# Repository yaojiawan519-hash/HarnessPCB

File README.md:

# HarnessPCB

**在自己的 Claude Code 里设计 PCB**：喂三段意图报告（原理图设计表 / 放置意图 /
布线意图），LLM 决策层调度执行器完成全链，产出可送厂的 Gerber。

> 状态：🟢 P0–P5 已完成（执行器抽取 + 双仓字节级复现 + 8 Skills + plugin 骨架
> + MCP server 随包 + 数据剥离审计 + MIT 许可；**P5 = 退役 RL 放置线、换规则摆件、
> 108 块人画电路块随包**），当前 **v0.2**。

## 快速开始（一屏）

前置：KiCad 10、Java 25+、FreeRouting v2.3.0（jar 从
[GitHub Releases](https://github.com/freerouting/freerouting/releases) 下，
放大磁盘任意位置）、Node 18+、[uv](https://docs.astral.sh/uv/)。

```bash
git clone <本仓库> && cd HarnessPCB

# 1. 装依赖（生成 executors/Placement/.venv；v0.2 起不再需要 torch——放置是纯规则）
cd executors/Placement && uv sync && cd ../..

# 2. 写本机工具路径（通常只需改 java / jar 两键；MCP server 已随包）
cat > ~/.harnesspcb.json <<'EOF'
{
  "HWS_KICAD_CLI": "/Applications/KiCad/KiCad.app/Contents/MacOS/kicad-cli",
  "HWS_KICAD_PY":  "/Applications/KiCad/KiCad.app/Contents/Frameworks/Python.framework/Versions/3.9/bin/python3.9",
  "HWS_KICAD_EXT": "/Applications/KiCad/KiCad.app/Contents",
  "HWS_JAVA": "/opt/homebrew/opt/openjdk@26/bin/java",
  "HWS_FREEROUTING_JAR": "/path/to/freerouting.jar",
  "D2S_MCP": "<克隆目录>/mcp/server/index.mjs",
  "D2S_NODE": "/opt/homebrew/bin/node"
}
EOF

# 3. 体检（全绿才继续；三级解析：环境变量 > 此文件 > 标准探测）
executors/Placement/.venv/bin/kca doctor

# 4. 跑包内 demo 全链（设计表 → 原理图 → 放置 → 布线 → 铺铜 → DRC）
python3 executors/SchematicDesign/design2schematic/d2s.py chain \
  -d demo/demo_blinker.design.json -o demo/out \
  --clearances 205,215,225,235,245 --mp 60
```

demo 是什么、期望产物链，见 `demo/README.md`。全绿后按
`skills/pcb-fab-export` 出 Gerber。设计表写法看 `docs/输入格式说明.md`。

## 装成 Claude Code 插件

上面是裸 CLI 形态。装成插件后，Skills 与斜杠命令自动可用：

```bash
# 方式 A：本地路径（开发/试用）
claude plugin marketplace add /path/to/HarnessPCB
claude plugin install harnesspcb@harnesspcb

# 方式 B：git URL（仓库推上远端后）
claude plugin marketplace add <git-url>
claude plugin install harnesspcb@harnesspcb
```

装好后在本项目里：

| 命令 | 干什么 |
|---|---|
| `/harnesspcb:pcb-demo` | 跑包内 demo 全链，验证环境 |
| `/harnesspcb:pcb-run <design.json>` | 跑一块用户板全链（可带 `--intent`） |
| `/harnesspcb:pcb-new [需求]` | 从需求访谈 → 设计表 → 意图 → 全链出板 |

8 个 Skills（`pcb-chain` / `pcb-place` / `pcb-route` / `pcb-route-session` /
`pcb-intent-spec` / `pcb-drc-read` / `pcb-silk-tidy` / `pcb-fab-export`）
随插件自动装配；裸 CLI 形态则把 `skills/` 拷（或 symlink）进项目
`.claude/skills/`。各 skill 何时用见下表。

## Skills 一览（8 个）

| Skill | 何时用 |
|---|---|
| `pcb-chain` | 一条命令全链（sch→board→place→route→pour→DRC），默认入口 |
| `pcb-place` / `pcb-route` | 单独重跑放置（规则摆件，调 `--face`/`--gap`/`--ports`）/ 布线（调阶梯、看真数） |
| `pcb-route-session` | 剩余死网手术：candidates/blockers/单网重布/快照回滚 |
| `pcb-intent-spec` | 放置的写前清单 + 交付审查对照（原「意图 spec」，spec 本身已停用） |
| `pcb-drc-read` | DRC 报告口径（铜级 9 类 / 容忍项 / fail-closed） |
| `pcb-silk-tidy` | 丝印清理五条方法学（美观项，不挡验收） |
| `pcb-fab-export` | Gerber + 钻孔 + 贴片坐标导出打包 |

## 块库（108 块）

`blocks/` 里是从真实开源板**一件一件、一截铜一截铜扣下来**的电路：原理图、封装、
人手画的走线原封不动。设计新板时当**菜单**用——能整块复用的别重画。

```bash
ls blocks/                      # 每块一个目录
cat blocks/INDEX.md             # 人看：块名 / 类别 / 件数 / 铜量 / 来源板 / 许可
python3 -c "import json;[print(b['name'],b['category']) for b in json.load(open('blocks/index.json'))['blocks']]"
```

每块带块卡（端口 / 轨 / 内部网 / 出处与许可）与实测几何。**口岸按焊盘记**：
拼板时从焊盘重新拉线，不指望块里切剩的出口铜对接上。GND 与电源轨在块里是裂开的
（块不带铺铜），拼板必须整板重铺。规矩与坑详见 `docs/块库说明.md`。

只收可公开发行的块（MIT/Apache 等）；用户自己的板与许可未核定的块**不在本仓库**。

## 仓库结构

| 目录 | 内容 |
|---|---|
| `skills/` | 8 个操作 Skills（上表） |
| `commands/` | 插件斜杠命令（pcb-demo / pcb-run / pcb-new） |
| `.claude-plugin/` + `.mcp.json` | Claude Code plugin 清单与 MCP 声明 |
| `mcp/` | 随包 KiCad MCP server（单文件 bundle + python 接口层，源自 KiCAD-MCP-Server v2.7.0，MIT，见 `mcp/LICENSE-KiCAD-MCP-Server`） |
| `executors/` | 白名单抽取的执行器（d2s / 规则摆件 place_rules / route 冻结梯子 / actions / 块工具链 sdi + IL 解析层），`MANIFEST.json` 逐文件 sha256 |
| `blocks/` | **108 块人画电路块**（原理图 + 板 + 块卡 + 实测几何），可整块复用；见 `docs/块库说明.md` |
| `docs/` | 输入格式说明、块库说明、参数快照 FLAG_FREEZE |
| `demo/` | 合成 demo 板（设计表 + 期望产物说明） |
| `tools/` | 抽取脚本（`pack_from_studio.py` + allowlist、`pack_blocks.py`） |

## 同步机制（贡献者向）

```bash
python3 tools/pack_from_studio.py --check   # 看差异（缺/多/变动）
python3 tools/pack_from_studio.py --sync    # 重生成 executors/ + MANIFEST.json

python3 tools/pack_blocks.py --list         # 谁进包、谁被许可证挡下
python3 tools/pack_blocks.py --check        # 块库差异
python3 tools/pack_blocks.py --sync         # 重生成 blocks/ + 索引 + MANIFEST-blocks.json
```

块库**按许可证筛**而不是按路径：只收 `license_tier: permissive`，`internal`
（用户自己的板 / 许可未核定）与无块卡的老块整批拒绝——公开仓放不起这个错。

`executors/` 由抽取脚本从开发工作台（母舰）生成，**禁止手改**（下次同步会被
覆盖）；`skills/`、`docs/`、`demo/`、`commands/`、`.claude-plugin/` 的权威源
在本仓库，直接在此编写。一切代码与测试在母舰工作台进行，单向同步进本仓库，
绝不反向修改。allowlist 从 Skills 调用面自下而上反推（`tools/allowlist.txt`
是唯一清单源），评估产物 / 用户板 / RL 权重 / 研究脚本结构上就进不来。

## 外部依赖与版本口径

| 依赖 | 版本口径 | 用途 |
|---|---|---|
| KiCad | 10（macOS Apple Silicon 实测；他平台未验） | pcbnew Python API、kicad-cli |
| FreeRouting | **v2.3.0 钉死**（需 Java 25+，调用内部钉单线程） | 布线 |
| KiCAD-MCP-Server | v2.7.0（已随包 bundle，MIT） | 原理图步的 KiCad 桥 |
| Node | 18+（实测 25） | 起 MCP server |
| uv | 任意近期版 | 建 Python 环境 |

## 许可

- 本仓库代码与文档：**MIT**（见根目录 `LICENSE`）。
- 随包 `mcp/`：源自 KiCAD-MCP-Server（MIT），原许可文件保留于
  `mcp/LICENSE-KiCAD-MCP-Server`。
- **FreeRouting 不随包分发**：它是 GPL-3.0，与本包 MIT 不兼容，故 jar
  由使用者自行从官方 [GitHub Releases](https://github.com/freerouting/freerouting/releases)
  下载，包内只含调用接口（`HWS_FREEROUTING_JAR` 指向你自己的 jar）。

所有工具路径**三级解析**：环境变量（`HWS_*` / `D2S_*`）> 机器配置文件
`~/.harnesspcb.json`（`HWS_CONFIG` 可改指）> 标准探测（PATH / 常见安装位）。
`kca doctor` 一条命令体检全链缺项。推荐档参数以
`docs/参数快照_FLAG_FREEZE.md` 为唯一权威源。

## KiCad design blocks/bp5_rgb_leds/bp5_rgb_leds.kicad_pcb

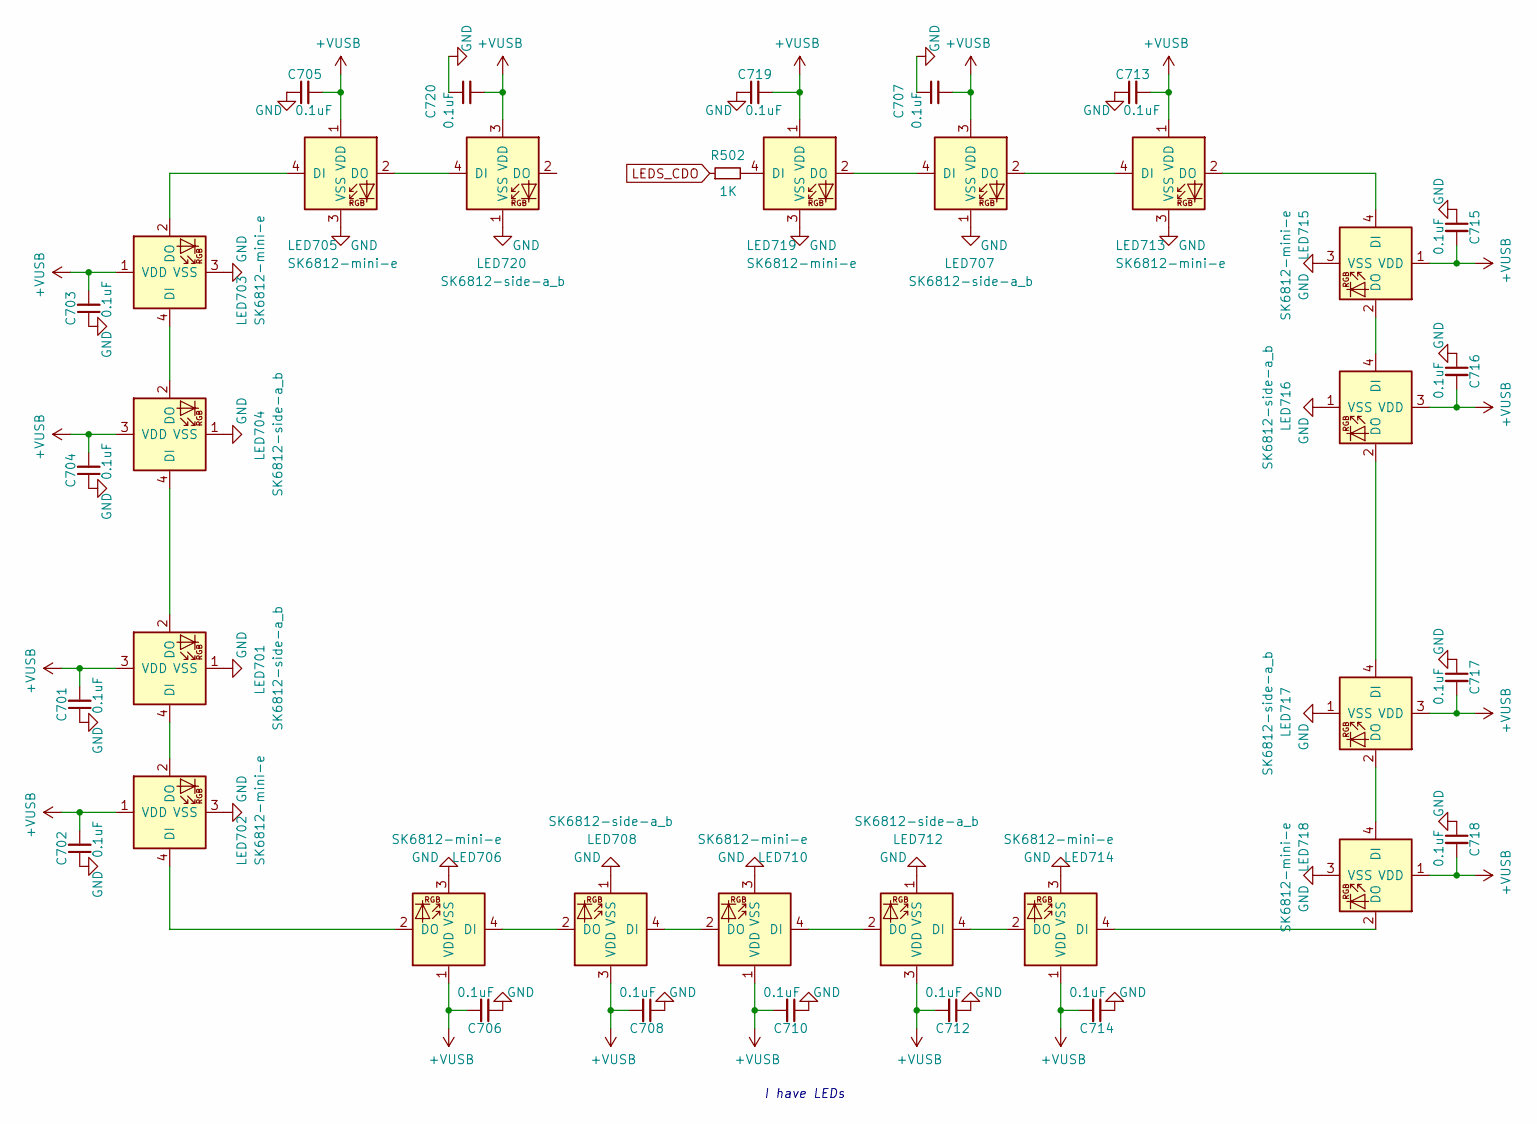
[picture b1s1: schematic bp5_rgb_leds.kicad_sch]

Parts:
C701, C702, C703, C704, C705, C706, C707, C708, C710, C712, C713, C714, C715, C716, C717, C718, C719, C720: 0.1uF; C_0402_1005Metric
LED701, LED704, LED707, LED708, LED712, LED716, LED717, LED720: SK6812-side-a_b
LED702, LED703, LED705, LED706, LED710, LED713, LED714, LED715, LED718, LED719: SK6812-mini-e
R502: 1K; R_0402_1005Metric

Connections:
+VUSB: C701.2, C702.2, C703.2, C704.2, C705.2, C706.2, C707.2, C708.2, C710.2, C712.2, C713.2, C714.2, C715.2, C716.2, C717.2, C718.2, C719.2, C720.2, LED701.3 (VDD), LED702.1 (VDD), LED703.1 (VDD), LED704.3 (VDD), LED705.1 (VDD), LED706.1 (VDD), LED707.3 (VDD), LED708.3 (VDD), LED710.1 (VDD), LED712.3 (VDD), LED713.1 (VDD), LED714.1 (VDD), LED715.1 (VDD), LED716.3 (VDD), LED717.3 (VDD), LED718.1 (VDD), LED719.1 (VDD), LED720.3 (VDD)
GND: C701.1, C702.1, C703.1, C704.1, C705.1, C706.1, C707.1, C708.1, C710.1, C712.1, C713.1, C714.1, C715.1, C716.1, C717.1, C718.1, C719.1, C720.1, LED701.1 (VSS), LED702.3 (VSS), LED703.3 (VSS), LED704.1 (VSS), LED705.3 (VSS), LED706.3 (VSS), LED707.1 (VSS), LED708.1 (VSS), LED710.3 (VSS), LED712.1 (VSS), LED713.3 (VSS), LED714.3 (VSS), LED715.3 (VSS), LED716.1 (VSS), LED717.1 (VSS), LED718.3 (VSS), LED719.3 (VSS), LED720.1 (VSS)
LEDS_CDO: R502.1
unnamed: LED701.4 (DI), LED702.2 (DO)
unnamed: LED701.2 (DO), LED704.4 (DI)
unnamed: LED702.4 (DI), LED706.2 (DO)
unnamed: LED703.4 (DI), LED704.2 (DO)
unnamed: LED703.2 (DO), LED705.4 (DI)
unnamed: LED705.2 (DO), LED720.4 (DI)
unnamed: LED706.4 (DI), LED708.2 (DO)
unnamed: LED707.4 (DI), LED719.2 (DO)
unnamed: LED707.2 (DO), LED713.4 (DI)
unnamed: LED708.4 (DI), LED710.2 (DO)
unnamed: LED710.4 (DI), LED712.2 (DO)
unnamed: LED712.4 (DI), LED714.2 (DO)
unnamed: LED713.2 (DO), LED715.4 (DI)
unnamed: LED714.4 (DI), LED718.2 (DO)
unnamed: LED715.2 (DO), LED716.4 (DI)
unnamed: LED716.2 (DO), LED717.4 (DI)
unnamed: LED717.2 (DO), LED718.4 (DI)
unnamed: LED719.4 (DI), R502.2

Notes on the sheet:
I have LEDs

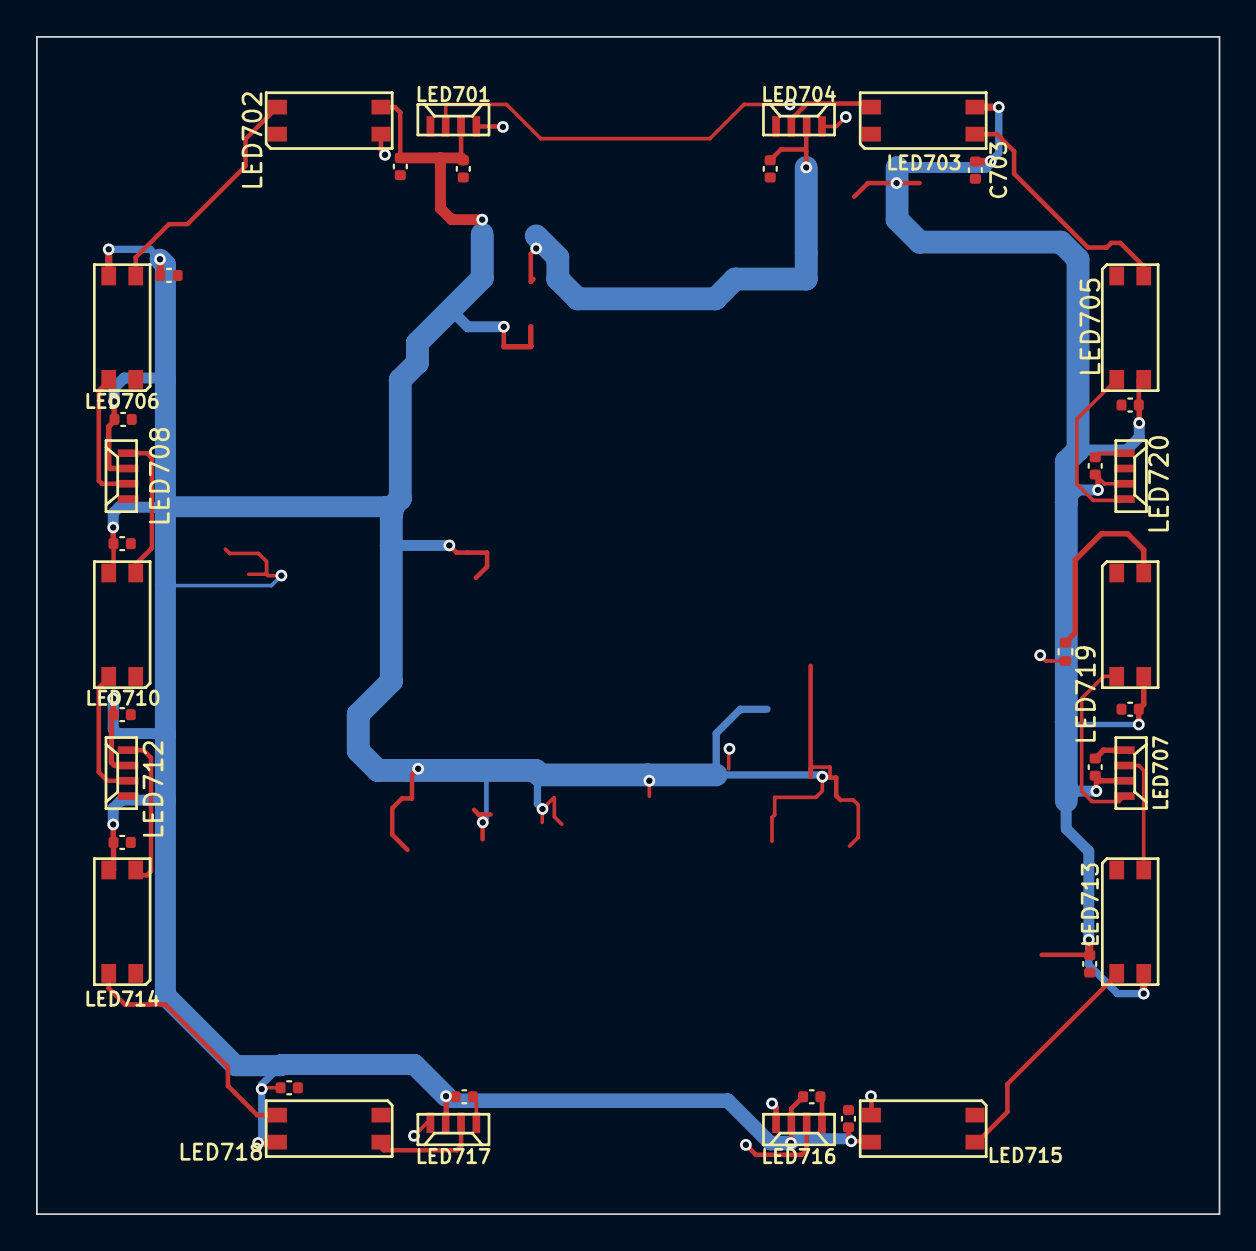
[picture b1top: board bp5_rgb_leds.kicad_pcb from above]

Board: 4 copper layers, 65.7 x 65.4 mm, 37 parts (0 on the bottom side), 20 nets.

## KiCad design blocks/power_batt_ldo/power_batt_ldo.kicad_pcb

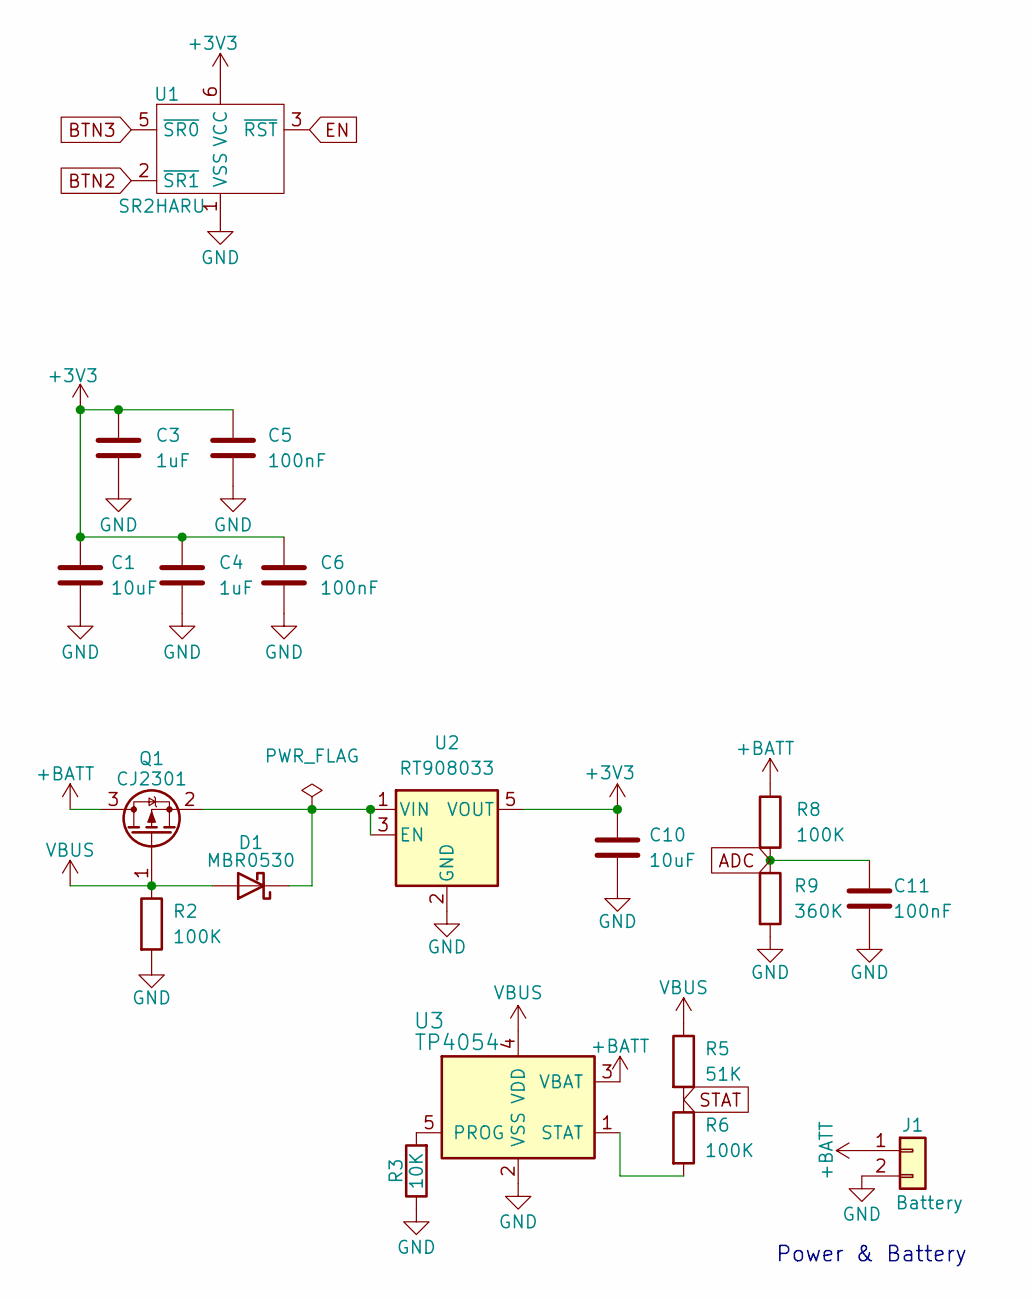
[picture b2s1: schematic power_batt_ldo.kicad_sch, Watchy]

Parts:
C1, C10: 10uF; C_0402_1005Metric
C3, C4: 1uF; C_0402_1005Metric
C5, C6, C11: 100nF; C_0402_1005Metric
D1: MBR0530; D_SOD-123
J1: Battery; 1.25T-2PWT (Molex 532610271)
Q1: CJ2301; SOT-23
R2, R6, R8: 100K; R_0402_1005Metric
R3: 10K; R_0402_1005Metric
R5: 51K; R_0402_1005Metric
R9: 360K; R_0402_1005Metric
U1: SR2HARU
U2: RT908033; SOT-23-5
U3: TP4054; SOT-23-5

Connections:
+3V3: C1.1, C3.1, C4.1, C5.1, C6.1, C10.1, U1.6 (VCC), U2.5 (VOUT)
+BATT: J1.1, Q1.3 (D), R8.1, U3.3 (VBAT)
ADC: C11.1, R8.2, R9.1
BTN2: U1.2 (~SR1)
BTN3: U1.5 (~SR0)
EN: U1.3 (~RST)
GND: C1.2, C3.2, C4.2, C5.2, C6.2, C10.2, C11.2, J1.2, R2.2, R3.1, R9.2, U1.1 (VSS), U2.2 (GND), U3.2 (VSS)
unnamed: D1.1 (K), Q1.2 (S), U2.1 (VIN), U2.3 (EN)
unnamed: R3.2, U3.5 (PROG)
unnamed: R6.2, U3.1 (STAT)
STAT: R5.2, R6.1
VBUS: D1.2 (A), Q1.1 (G), R2.1, R5.1, U3.4 (VDD)

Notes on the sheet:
Power & Battery

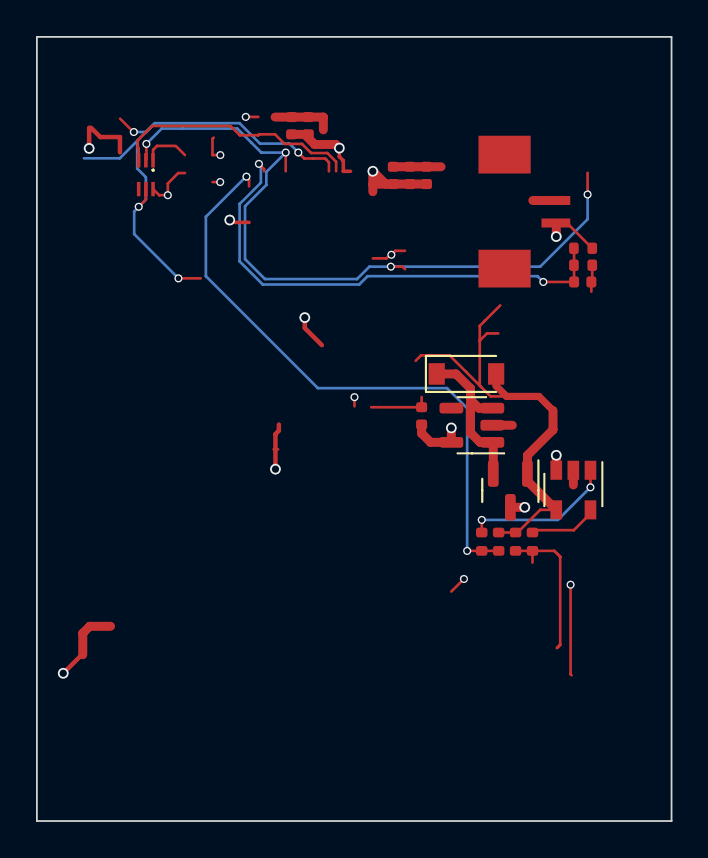
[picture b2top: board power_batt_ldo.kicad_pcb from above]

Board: 4 copper layers, 35.3 x 43.6 mm, 19 parts (0 on the bottom side), 9 nets.

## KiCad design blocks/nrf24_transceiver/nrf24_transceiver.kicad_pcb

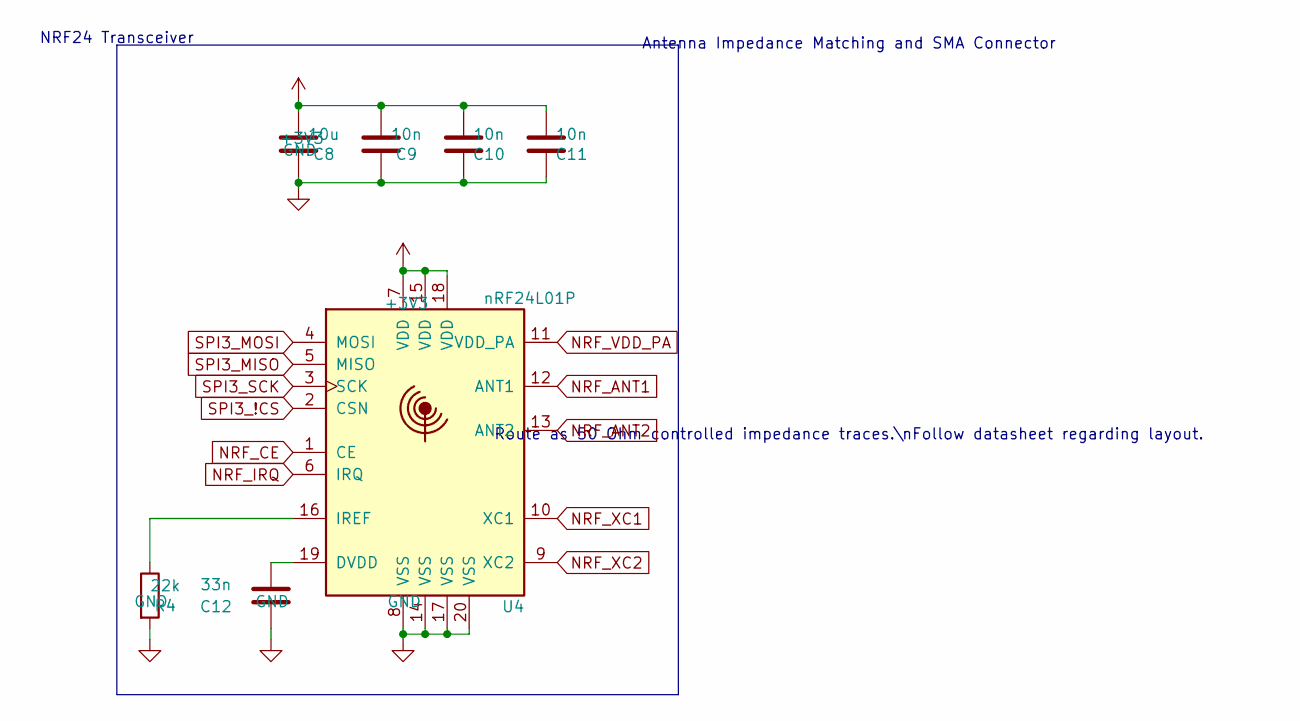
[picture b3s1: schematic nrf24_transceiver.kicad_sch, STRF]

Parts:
C8: 10u; C_0603_1608Metric
C9, C10, C11: 10n; C_0402_1005Metric
C12: 33n; C_0402_1005Metric
R4: 22k; R_0402_1005Metric
U4: nRF24L01P; QFN-20-1EP_4x4mm_P0.5mm_EP2.5x2.5mm

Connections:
+3V3: C8.1, C9.1, C10.1, C11.1, U4.7 (VDD), U4.15 (VDD), U4.18 (VDD)
GND: C8.2, C9.2, C10.2, C11.2, C12.2, R4.2, U4.8 (VSS), U4.14 (VSS), U4.17 (VSS), U4.20 (VSS), U4.21
NRF_ANT1: U4.12 (ANT1)
NRF_ANT2: U4.13 (ANT2)
NRF_CE: U4.1 (CE)
NRF_IRQ: U4.6 (IRQ)
NRF_VDD_PA: U4.11 (VDD_PA)
NRF_XC1: U4.10 (XC1)
NRF_XC2: U4.9 (XC2)
unnamed: C12.1, U4.19 (DVDD)
unnamed: R4.1, U4.16 (IREF)
SPI3_!CS: U4.2 (CSN)
SPI3_MISO: U4.5 (MISO)
SPI3_MOSI: U4.4 (MOSI)
SPI3_SCK: U4.3 (SCK)

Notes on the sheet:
NRF24 Transceiver
Antenna Impedance Matching and SMA Connector
Route as 50 Ohm controlled impedance traces.\nFollow datasheet regarding layout.

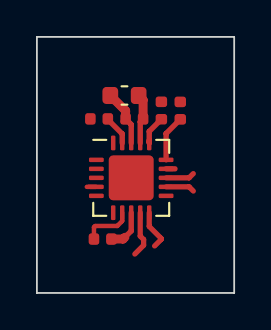
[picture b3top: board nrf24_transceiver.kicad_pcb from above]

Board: 2 copper layers, 11.0 x 14.2 mm, 7 parts (0 on the bottom side), 4 nets.

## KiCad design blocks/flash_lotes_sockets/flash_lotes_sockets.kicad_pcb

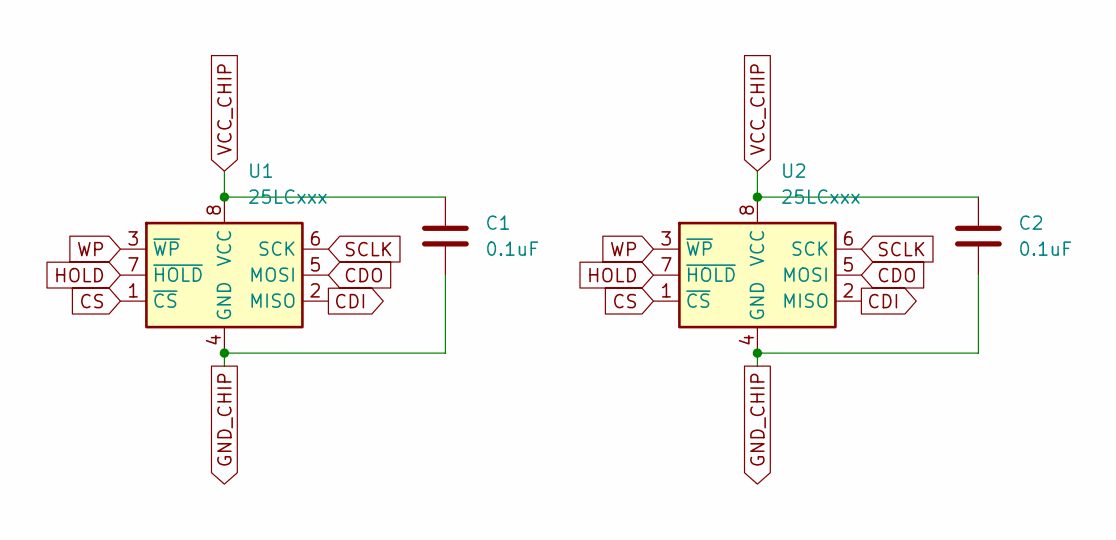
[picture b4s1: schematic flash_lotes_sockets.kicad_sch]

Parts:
C1, C2: 0.1uF; C_0805_2012Metric
U1: 25LCxxx; ASPI0001-P001A
U2: 25LCxxx; ACA-SPI-004-K01

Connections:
CDI: U1.2 (MISO), U2.2 (MISO)
CDO: U1.5 (MOSI), U2.5 (MOSI)
CS: U1.1 (~CS), U2.1 (~CS)
GND_CHIP: C1.2, C2.2, U1.4 (GND), U2.4 (GND)
HOLD: U1.7 (~HOLD), U2.7 (~HOLD)
SCLK: U1.6 (SCK), U2.6 (SCK)
VCC_CHIP: C1.1, C2.1, U1.8 (VCC), U2.8 (VCC)
WP: U1.3 (~WP), U2.3 (~WP)

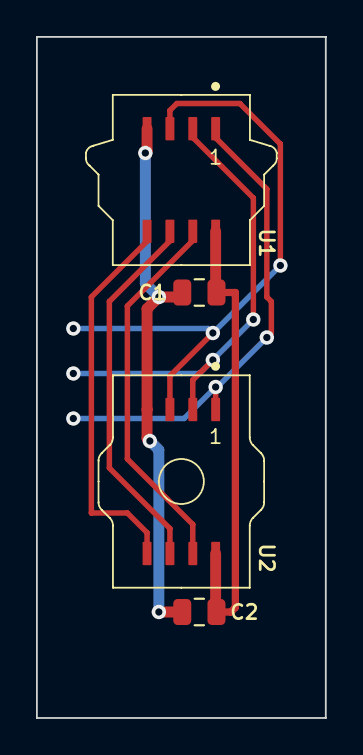
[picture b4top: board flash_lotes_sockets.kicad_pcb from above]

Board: 2 copper layers, 16.1 x 37.8 mm, 4 parts (0 on the bottom side), 8 nets.

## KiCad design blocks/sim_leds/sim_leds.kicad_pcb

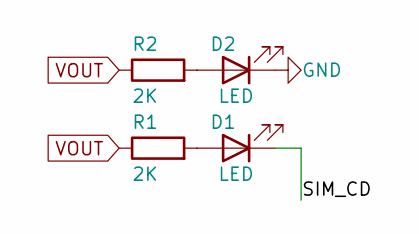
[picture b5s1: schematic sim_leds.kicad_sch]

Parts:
D1, D2: LED; LED_0805_2012Metric
R1, R2: 2K; R_0805_2012Metric

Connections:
GND: D2.1 (K)
unnamed: D1.2 (A), R1.2
unnamed: D2.2 (A), R2.2
VOUT: R1.1, R2.1

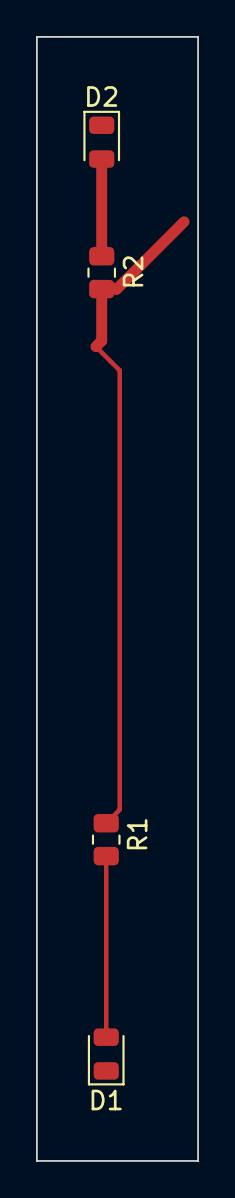
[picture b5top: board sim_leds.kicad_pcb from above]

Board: 2 copper layers, 9.0 x 62.4 mm, 4 parts (0 on the bottom side), 3 nets.

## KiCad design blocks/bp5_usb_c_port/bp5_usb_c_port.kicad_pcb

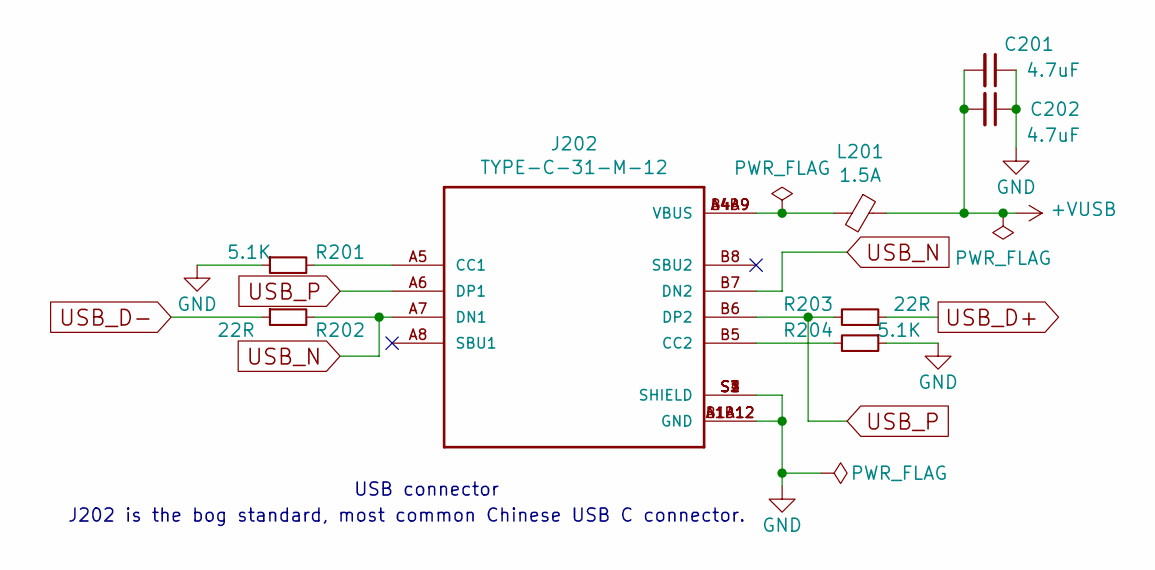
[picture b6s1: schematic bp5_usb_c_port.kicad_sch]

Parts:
C201, C202: 4.7uF; C_0402_1005Metric
J202: TYPE-C-31-M-12; HRO_TYPE-C-31-M-12
L201: 1.5A; L_0805_2012Metric
R201, R204: 5.1K; R_0402_1005Metric
R202, R203: 22R; R_0402_1005Metric

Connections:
+VUSB: C201.2, C202.2, L201.1
GND: C201.1, C202.1, J202.A1B12 (GND), J202.B1A12 (GND), J202.S1 (SHIELD), J202.S2 (SHIELD), J202.S3 (SHIELD), J202.S4 (SHIELD), R201.1, R204.1
unnamed: J202.A5 (CC1), R201.2
unnamed: J202.B5 (CC2), R204.2
unnamed: J202.A4B9 (VBUS), J202.B4A9 (VBUS), L201.2
USB_D+: R203.1
USB_D-: R202.1
USB_N: J202.A7 (DN1), J202.B7 (DN2), R202.2
USB_P: J202.A6 (DP1), J202.B6 (DP2), R203.2

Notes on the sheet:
USB connector
J202 is the bog standard, most common Chinese USB C connector.

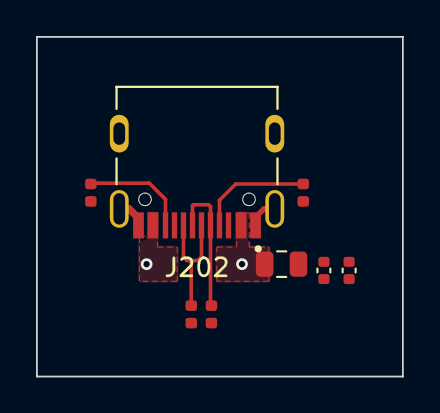
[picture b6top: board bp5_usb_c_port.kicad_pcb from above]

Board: 4 copper layers, 20.3 x 18.9 mm, 8 parts (0 on the bottom side), 7 nets.

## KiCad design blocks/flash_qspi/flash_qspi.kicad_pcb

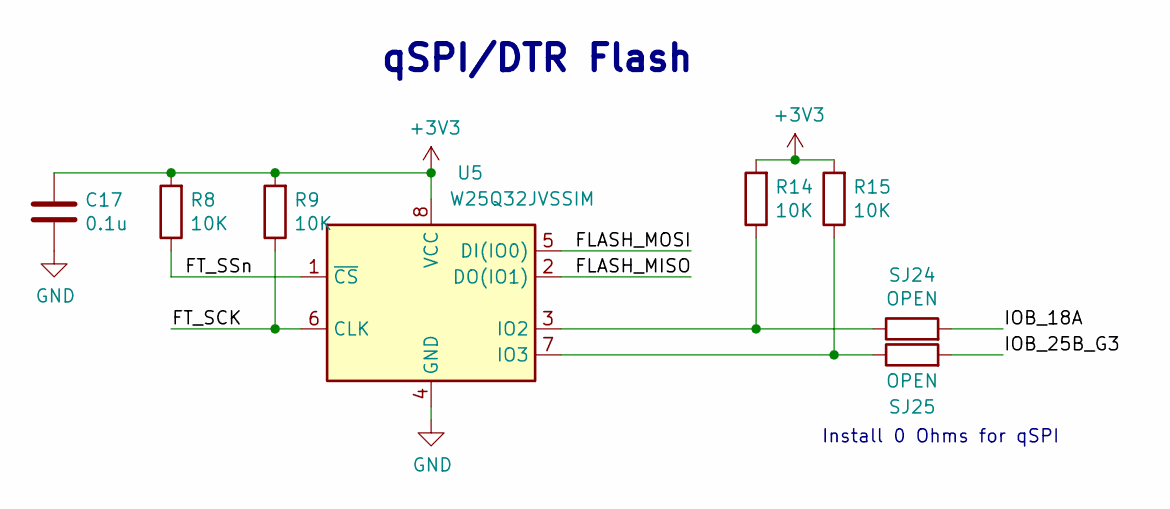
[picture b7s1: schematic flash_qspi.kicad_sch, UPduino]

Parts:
C17: 0.1u; C_0603_1608Metric
R8, R9, R14, R15: 10K; R_0603_1608Metric
SJ24, SJ25: OPEN; SolderJumper-2_0603_Open_TrianglePad1.0x1.5mm
U5: W25Q32JVSSIM; SOIC-8_5.23x5.23mm_P1.27mm

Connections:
+3V3: C17.1, R8.2, R9.2, R14.2, R15.2, U5.8 (VCC)
/FLASH_MISO: U5.2 (DO(IO1))
/FLASH_MOSI: U5.5 (DI(IO0))
/FT_SCK: R9.1, U5.6 (CLK)
/FT_SSn: R8.1, U5.1 (~CS)
/IOB_18A: SJ24.2
/IOB_25B_G3: SJ25.2
GND: C17.2, U5.4 (GND)
unnamed: R14.1, SJ24.1, U5.3 (IO2)
unnamed: R15.1, SJ25.1, U5.7 (IO3)

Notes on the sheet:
Install 0 Ohms for qSPI
qSPI/DTR Flash

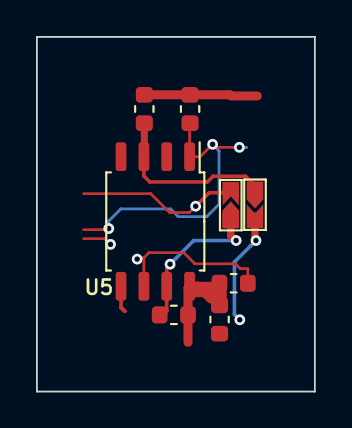
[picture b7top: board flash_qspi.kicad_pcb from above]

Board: 4 copper layers, 15.4 x 19.7 mm, 8 parts (0 on the bottom side), 6 nets.

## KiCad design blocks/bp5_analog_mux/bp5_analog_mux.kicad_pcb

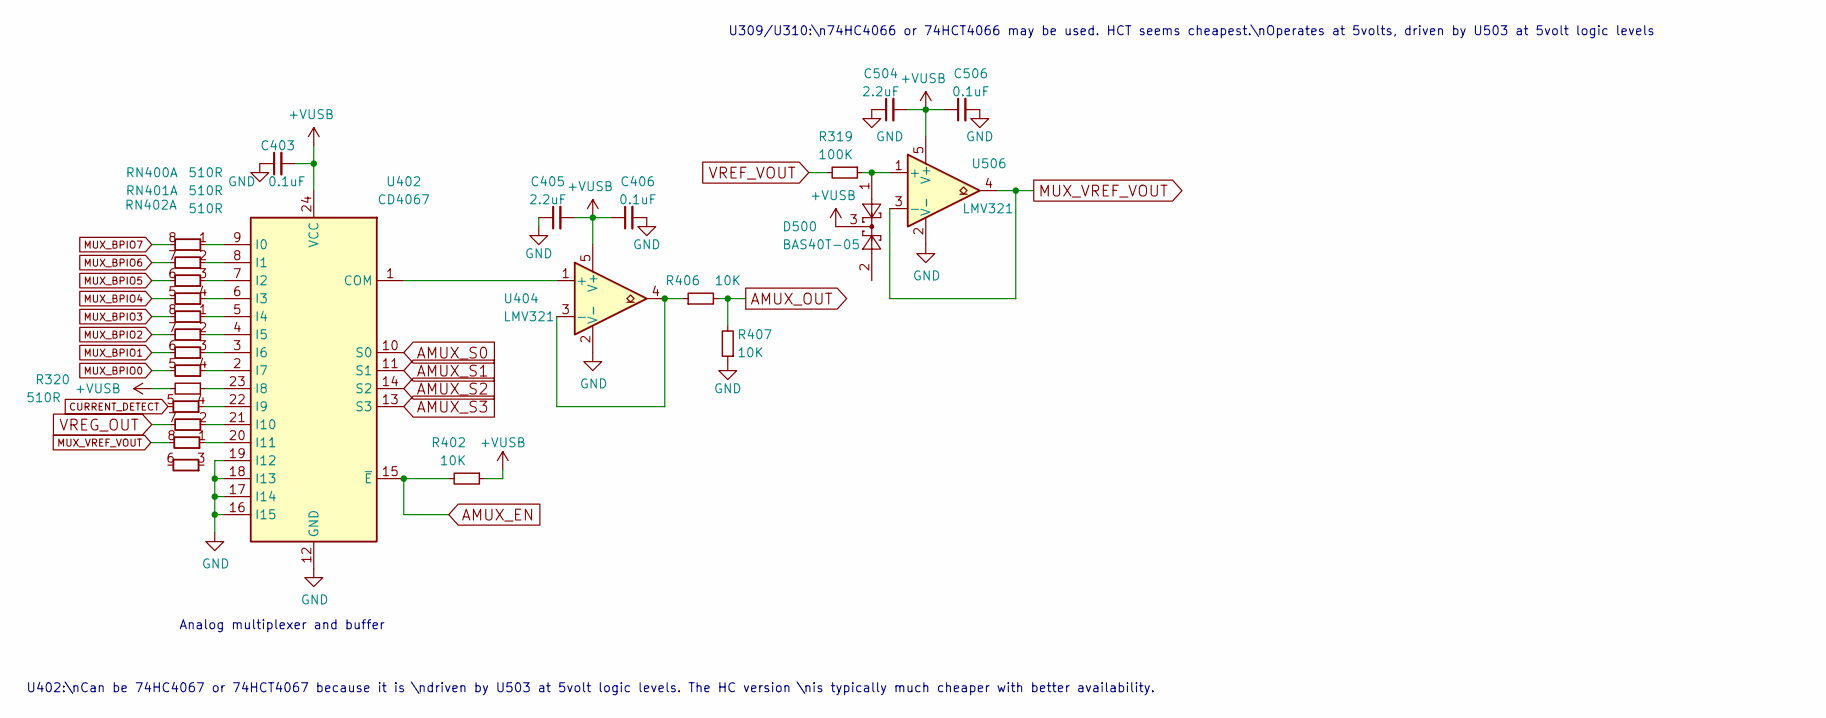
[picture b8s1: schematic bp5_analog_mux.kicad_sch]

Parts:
C403, C406, C506: 0.1uF; C_0402_1005Metric
C405, C504: 2.2uF; C_0402_1005Metric
D500: BAS40T-05; SOT-523
R319: 100K; R_0402_1005Metric
R320: 510R; R_0402_1005Metric
R402, R406, R407: 10K; R_0402_1005Metric
RN400, RN401, RN402: 510R; R_Array_Convex_4x0402
U402: CD4067; TSSOP-24_4.4x7.8mm_P0.65mm
U404, U506: LMV321; SOT-23-5

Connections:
+VUSB: C403.2, C405.2, C406.1, C504.2, C506.1, D500.3, R320.2, R402.1, U402.24 (VCC), U404.5 (V+), U506.5 (V+)
AMUX_EN: R402.2, U402.15 (~E)
AMUX_OUT: R406.2, R407.2
AMUX_S0: U402.10 (S0)
AMUX_S1: U402.11 (S1)
AMUX_S2: U402.14 (S2)
AMUX_S3: U402.13 (S3)
CURRENT_DETECT: RN402.5 (R1.8)
GND: C403.1, C405.1, C406.2, C504.1, C506.2, R407.1, U402.12 (GND), U402.16 (I15), U402.17 (I14), U402.18 (I13), U402.19 (I12), U404.2 (V-), U506.2 (V-)
MUX_BPIO0: RN401.5 (R1.8)
MUX_BPIO1: RN401.6 (R1.8)
MUX_BPIO2: RN401.7 (R1.8)
MUX_BPIO3: RN401.8 (R1.8)
MUX_BPIO4: RN400.5 (R1.8)
MUX_BPIO5: RN400.6 (R1.8)
MUX_BPIO6: RN400.7 (R1.8)
MUX_BPIO7: RN400.8 (R1.8)
MUX_VREF_VOUT: RN402.8 (R1.8), U506.3 (-), U506.4
unnamed: RN400.1 (R1.1), U402.9 (I0)
unnamed: RN400.2 (R1.1), U402.8 (I1)
unnamed: RN400.3 (R1.1), U402.7 (I2)
unnamed: RN400.4 (R1.1), U402.6 (I3)
unnamed: RN401.1 (R1.1), U402.5 (I4)
unnamed: RN401.2 (R1.1), U402.4 (I5)
unnamed: RN401.3 (R1.1), U402.3 (I6)
unnamed: RN401.4 (R1.1), U402.2 (I7)
unnamed: RN402.1 (R1.1), U402.20 (I11)
unnamed: RN402.2 (R1.1), U402.21 (I10)
unnamed: RN402.4 (R1.1), U402.22 (I9)
unnamed: U402.1 (COM), U404.1 (+)
unnamed: R320.1, U402.23 (I8)
unnamed: R406.1, U404.3 (-), U404.4
unnamed: D500.1, R319.1, U506.1 (+)
VREF_VOUT: R319.2
VREG_OUT: RN402.7 (R1.8)

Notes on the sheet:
Analog multiplexer and buffer
U402:\nCan be 74HC4067 or 74HCT4067 because it is \ndriven by U503 at 5volt logic levels. The HC version \nis typically much cheaper with better availability.
U309/U310:\n74HC4066 or 74HCT4066 may be used. HCT seems cheapest.\nOperates at 5volts, driven by U503 at 5volt logic levels

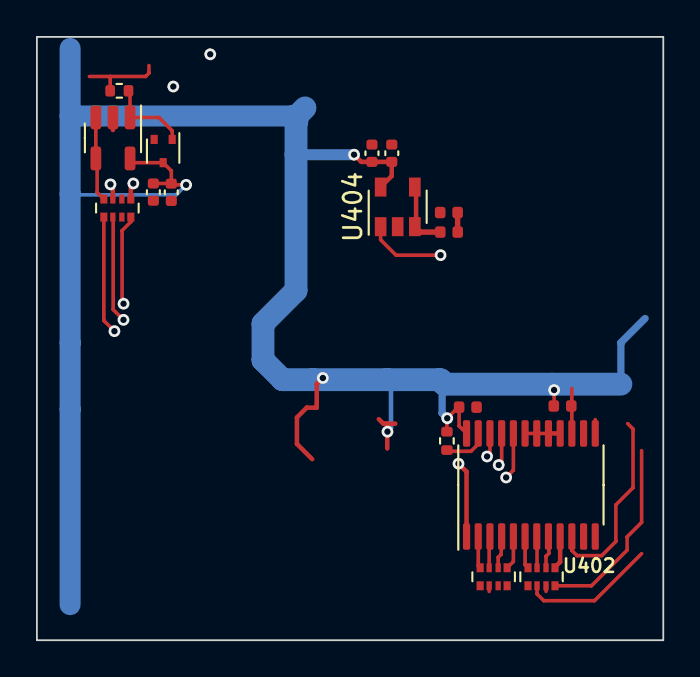
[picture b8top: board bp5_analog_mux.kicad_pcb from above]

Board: 4 copper layers, 34.8 x 33.5 mm, 17 parts (0 on the bottom side), 20 nets.

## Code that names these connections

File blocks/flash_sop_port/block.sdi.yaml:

project:
  kind: block
  name: flash_sop_port
  version: sdi/1
defs:
  flash_sop_port:
    category: connector
    rationale: '**适配板左侧"输入侧"**：J1 是 1×10 卧式母座（本体探出板左沿，套在 Bus Pirate 5 的排针上），J2 是同位的 1×10 竖排针，两只逐脚并联、实际只焊一只。
      十脚：**1=VOUT、2=VCC_PIN、3=GND_PIN、4=HOLD、5=WP、6=CDI、7=CS、8=SCLK、 9=CDO、10=GND**。两只 SPDT 开关决定芯片吃哪路电：SW1（VCC）
      **1=VCC_PIN、2=VCC_CHIP、3=VOUT**，SW2（GND）**1=GND、2=GND_CHIP、3=GND_PIN**。 十脚里其实是**两对独立电源**：1/10 号是
      `VOUT`/`GND`，2/3 号是 `VCC_PIN`/`GND_PIN`， 两对在本块里不相连，只在开关处二选一（⚠ SW1/SW2 必须拨到同一对）。 ⚠ 本块与 `flash_zif_port`
      的**电路逐网相同、几何不同**（那只板两只开关离得远 2mm 以上）。'
    ports:
    - name: CDI
      kind: signal
      class: digital
      direction: bidirectional
      exit:
        pin: J1-6
        connector: true
      pin: J1/6
      note: 第 6 脚 → 芯片 **MISO**（`CDI` 是主控侧叫法）；J1.6 与 J2.6 同网
    - name: CDO
      kind: signal
      class: digital
      direction: bidirectional
      exit:
        pin: J1-9
        connector: true
      pin: J1/9
      note: 第 9 脚 → 芯片 **MOSI**（Controller Data Out）；J1.9 / J2.9 同网
    - name: CS
      kind: signal
      class: digital
      direction: bidirectional
      exit:
        pin: J1-7
        connector: true
      pin: J1/7
      note: 第 7 脚（片选，低有效）
    - name: GND_CHIP
      kind: signal
      class: digital
      direction: bidirectional
      exit:
        pin: SW2-2
        connector: false
      pin: SW2/2
      note: ⚠ 出口脚是 **SW2 的中间脚**：芯片地从这里出去，进 SW2 前在 GND（第 10 脚）/ GND_PIN（第 3 脚）之间二选一
    - name: HOLD
      kind: signal
      class: digital
      direction: bidirectional
      exit:
        pin: J1-4
        connector: true
      pin: J1/4
      note: 第 4 脚（HOLD# / RESET#）
    - name: SCLK
      kind: signal
      class: digital
      direction: bidirectional
      exit:
        pin: J1-8
        connector: true
      pin: J1/8
      note: 第 8 脚（时钟）
    - name: VCC_CHIP
      kind: signal
      class: digital
      direction: bidirectional
      exit:
        pin: SW1-2
        connector: false
      pin: SW1/2
      note: ⚠ 出口脚是 **SW1 的中间脚**（不是排针脚）：芯片电源从这里出去，进 SW1 前在 VOUT / VCC_PIN 之间二选一
    - name: VOUT
      kind: signal
      class: digital
      direction: bidirectional
      exit:
        pin: J1-1
        connector: true
      pin: J1/1
      note: 第 1 脚：主机 VOUT 直入，也是电源灯的取电点（灯在另一个块里）；SW1.3 也在这根网上
    rails:
    - GND
    parts:
    - ref: SW1
      lib: Switch:SW_SPDT
      value: SW_SPDT
      footprint: Button_Switch_SMD:SW_SPDT_PCM12
    - ref: SW2
      lib: Switch:SW_SPDT
      value: SW_SPDT
      footprint: Button_Switch_SMD:SW_SPDT_PCM12
    - ref: J2
      lib: Connector_Generic:Conn_01x10
      value: Conn_01x10
      footprint: Connector_PinHeader_2.54mm:PinHeader_1x10_P2.54mm_Vertical
    - ref: J1
      lib: Connector_Generic:Conn_01x10
      value: Conn_01x10
      footprint: Connector_PinSocket_2.54mm:PinSocket_1x10_P2.54mm_Horizontal
    conns:
    - ref: J1
      pin: '6'
      net: CDI
    - ref: J2
      pin: '6'
      net: CDI
    - ref: J1
      pin: '9'
      net: CDO
    - ref: J2
      pin: '9'
      net: CDO
    - ref: J1
      pin: '7'
      net: CS
    - ref: J2
      pin: '7'
      net: CS
    - ref: J1
      pin: '10'
      net: GND
    - ref: J2
      pin: '10'
      net: GND
    - ref: SW2
      pin: '1'
      net: GND
    - ref: SW2
      pin: '2'
      net: GND_CHIP
    - ref: J1
      pin: '3'
      net: GND_PIN
    - ref: J2
      pin: '3'
      net: GND_PIN
    - ref: SW2
      pin: '3'
      net: GND_PIN
    - ref: J1
      pin: '4'
      net: HOLD
    - ref: J2
      pin: '4'
      net: HOLD
    - ref: J1
      pin: '8'
      net: SCLK
    - ref: J2
      pin: '8'
      net: SCLK
    - ref: SW1
      pin: '2'
      net: VCC_CHIP
    - ref: J1
      pin: '2'
      net: VCC_PIN
    - ref: J2
      pin: '2'
      net: VCC_PIN
    - ref: SW1
      pin: '1'
      net: VCC_PIN
    - ref: J1
      pin: '1'
      net: VOUT
    - ref: J2
      pin: '1'
      net: VOUT
    - ref: SW1
      pin: '3'
      net: VOUT
    - ref: J1
      pin: '5'
      net: WP
    - ref: J2
      pin: '5'
      net: WP
    placement_prior:
      anchor: J1
      max_mm: 6.0
      rationale: 左侧竖条 18.82×44.37mm：母座贴左沿、竖针在其右侧 3.80mm，SW1 在上（y≈68）、 SW2 在下（y≈106）。复用要点同 `flash_zif_port`：开口朝板外、这块板要骑在主机排针上。
    slots: []
    hot_loop: []
    internal_nets:
    - GND_PIN
    - VCC_PIN
    - WP
    provenance:
      source: human:open-source
      board: Bus Pirate 5 flash adapter (SOP) REV3
      license: MIT — 上游 Copyright (c) 2023 Ian Lesnet / Where Labs LLC
      license_tier: permissive
      author: Dangerous Prototypes（上游）/ HarnessPCB（裁块）
      date: '2026-10-30'
      kicad: 10.0.5
      basis: 4 件 / 12 网 / 端口 8 + 轨 1；铜 48 段 + 3 孔；死铜删 11；口岸切口 6；卡↔板门 ①~⑤ 全过
    geometry_status: 'extracted 2026-10-30 kicad 10.0.5（PCB 从 flash-sop-rev3.kicad_pcb 原样扣，坐标 = 源板坐标平移，origin:
      page；源板那张双面 **GND_CHIP** 灌铜（芯片侧地，不是板上 GND）是整板口岸网，按「块内不带铺铜」整张删，拼板时由整板铺铜接上）'
    notes:
    - '**适配板左侧"输入侧"**：J1 是 1×10 卧式母座（`PinSocket_1x10_P2.54mm_Horizontal`，本体探出板左沿 9.09mm、套在 Bus Pirate
      5 的排针上），J2 是同位的 1×10 竖排针（`PinHeader_1x10_P2.54mm_Vertical`），两只逐脚并联、实际只焊一只。十脚：**1=VOUT、2=VCC_PIN、3=GND_PIN、4=HOLD、5=WP、6=CDI、7=CS、8=SCLK、9=CDO、10=GND**。'
    - ⚠ `CDI` / `CDO` 是**主控侧**的名字（Controller Data In / Out）：`CDI` 接芯片的 **MISO**、`CDO` 接芯片的 **MOSI**——与芯片手册上的
      MOSI/MISO 正好相反。照名字直连会把主控的输入接到芯片的输入上。
    - 两只 SPDT 开关决定**芯片吃哪路电**：SW1（VCC）**1=VCC_PIN、2=VCC_CHIP、3=VOUT**，SW2（GND）**1=GND、2=GND_CHIP、3=GND_PIN**。所以
      `VCC_CHIP` / `GND_CHIP` 这两个端口的出口脚是**开关的中间脚**（SW1.2 / SW2.2），不是排针脚——拼板时接的就是这两个脚。⚠ 两只开关**必须拨到同一对**（都选
      VOUT/GND，或都选 VCC_PIN/GND_PIN），拨混了芯片的电源与地来自两对不同的源。
    - ⚠ 十脚里其实是**两对独立电源**：1/10 号是 `VOUT`/`GND`（主机直供的一对），2/3 号是 `VCC_PIN`/`GND_PIN`（另一对）。两对在本块里不相连，只在开关处二选一。
    - ⚠ `WP`（排针第 5 脚）在**本版到不了座**：这一族 ZIF / 16 脚 / 20 脚测试座上都**没有** WP 触点，它只连到 J1.5 ↔ J2.5 两个排针脚就断了（卡里登记为块内网
      `WP`，拼装时逐实例改名、别当端口）。要控写保护，得自己从排针第 5 脚飞一根线到芯片的 WP# 那一脚——这正是本版与 lotes / wson 两版（WP 真的到焊位）最实用的一处电路差别。
    - 几何：J1 @(138.44, 75.41) rot 0、J2 @(142.24, 75.44) rot 0（x 差 3.80mm、y 差 0.03mm，两列脚一一对齐）；SW1 @(142.24,
      68.25) rot 180、SW2 @(142.24, 105.78) rot 0。块 20.1×47.72mm（J1 的封装框从 x=127.86 起，比板左沿还外 9.09mm——这块板是**骑在**主机排针上的）。复用要点：母座开口朝板外、竖针朝上；复制块时朝向一起搬。
    - ⚠ 同族对照：本块与 `flash_zif_port` **逐件同坐标**（J1/J2/SW1/SW2 的 x/y/rot 全同），两块可以互换；铜略有差别（本块 60 段 + 6 孔，那只
      61 段 + 5 孔）。四块 `*_port` 里 J1/J2 处处相同，**只有 SW1/SW2 的 y 会动**（这一族差 1.85mm），所以四块都得按板各留一份，不能共用一个块。
    - '⚠ 这一族四张板子的**灌铜是 `GND_CHIP`（芯片侧地），不是 `GND`**。所以「块内不带铺铜」删掉的是芯片地，裂岛/裸脚全落在 `GND_CHIP` 上；`GND`（排针第 10
      脚、灯的回流）本来就没有铺铜，只靠走线。卡里 `GND_CHIP` 记在 **ports** 下、`kind: signal`——那是引擎的规则（rails 只收电源符号 `#PWR`，本板作者用的是全局标签）；它电学上是**芯片的电源/地网**，拼板时按同名接，别当信号口去串阻容。'
    - 铜 48 段 + 3 孔（B 8 / F 52）；死铜删 11 段/孔（两端全悬空、谁也连不上的才算）；口岸切口 6 处（一端悬空=块的铜接口，按用户拍板留着）、走线出口 7 处；削剩残迹留
      4 段（残迹长度只是窗口参数的函数、不是人的设计）；铺铜带走 0 张（源板那张双面 GND_CHIP 灌铜是整板口岸网，按「块内不带铺铜」整张删，拼板时重铺）。
    - 块里每个脚都有铜可接（没有"只靠铺铜连"的焊盘）。
    - 本块的铜有 1 处止在**块外器件**的焊盘上（VOUT->R1.1→1）：那几只焊盘不在这块里（`VOUT→R1.1` 就是电源灯的那颗电阻），块单看这一头是断的，拼板时接上就通。
    - kicad-cli DRC：isolated_copper 0；未连通 **0** 条；断头走线 7 + 悬空过孔 3 处就是"口岸切口"（铜走到窗口边就停 = 块的铜接口，留着）；lib_footprint_*
      2 条（源板自带，见基线）；源板 flash-sop-rev3.kicad_pcb 基线：未连通 0 / isolated_copper 0 / 违规 64 条。
